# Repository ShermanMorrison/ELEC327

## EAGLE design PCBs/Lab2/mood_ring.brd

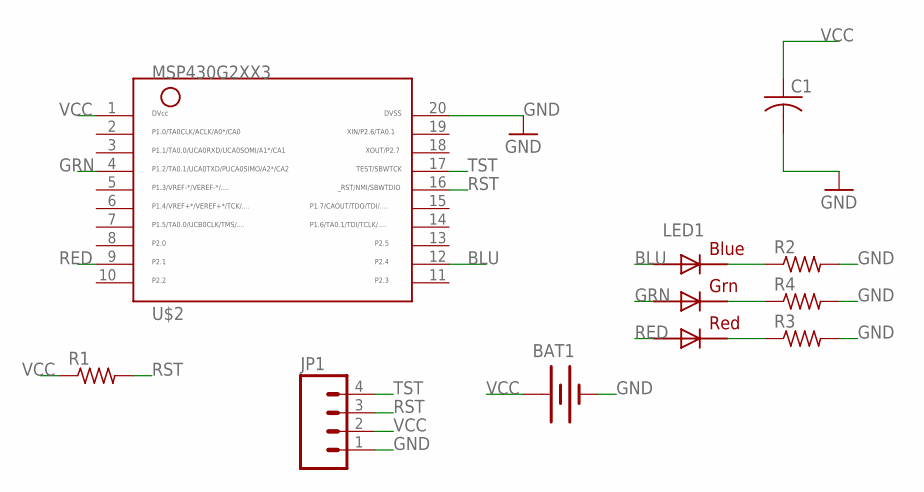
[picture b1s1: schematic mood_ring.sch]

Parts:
BAT1: BATTERYBU2032SM; BU2032SM
C1: C-USC1206; C1206
JP1: M04LOCK; 1X04_LOCK
LED1: RGBLED5050
R1, R2, R3, R4: R-US_R1206; R1206
U$2: MSP430G2XX3TSSOP; PW20

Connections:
BLU: LED1.3 (BLUE_A), U$2.12
GND: BAT1.P$2 (-), C1.2, JP1.1, R2.2, R3.2, R4.2, U$2.20
GRN: LED1.1 (GREEN_A), U$2.4
unnamed: LED1.4 (BLUE_C), R2.1
unnamed: LED1.5 (RED_C), R3.1
unnamed: LED1.6 (GREEN_C), R4.1
RED: LED1.2 (RED_A), U$2.9
RST: JP1.3, R1.2, U$2.16
TST: JP1.4, U$2.17
VCC: BAT1.P$1 (+), C1.1, JP1.2, R1.1, U$2.1

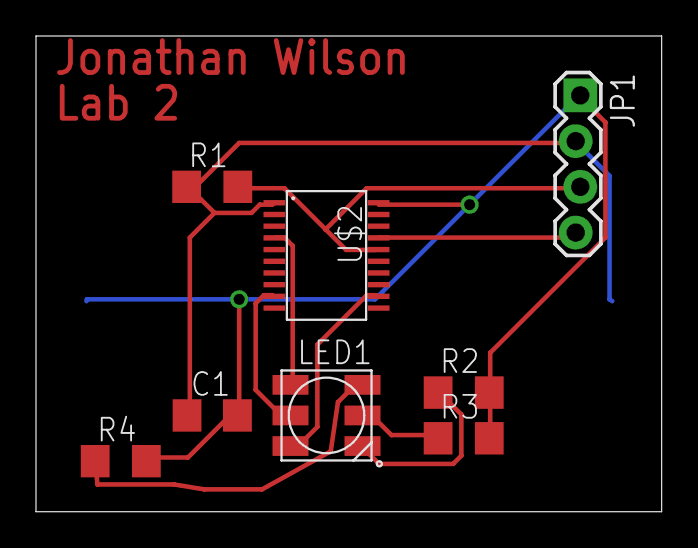
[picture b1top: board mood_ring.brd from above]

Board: 2 copper layers, 34.8 x 26.4 mm, 9 parts (1 on the bottom side), 10 nets.

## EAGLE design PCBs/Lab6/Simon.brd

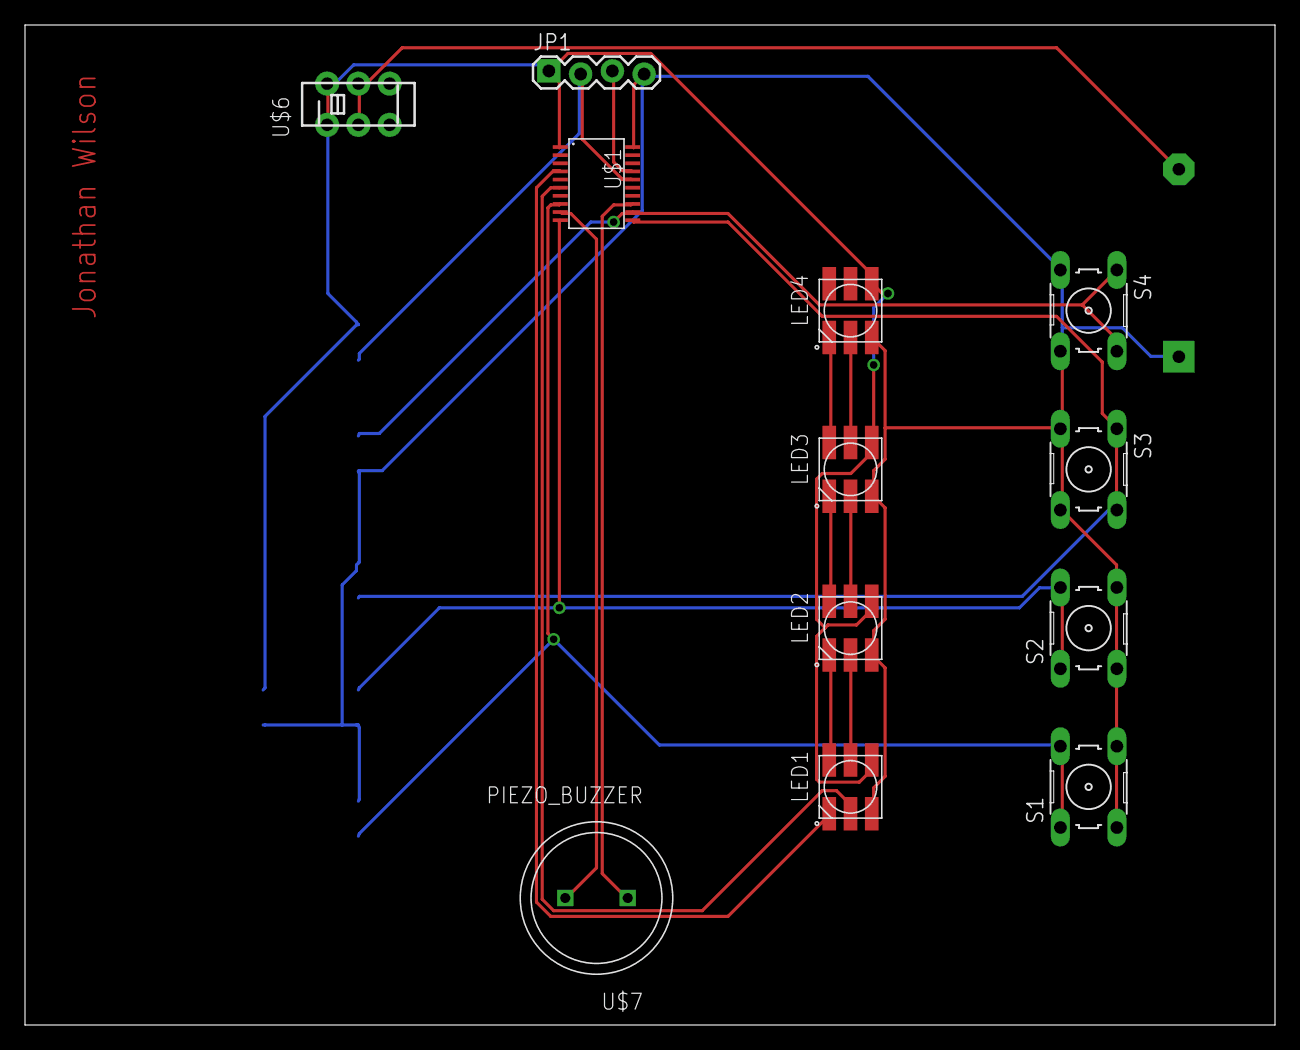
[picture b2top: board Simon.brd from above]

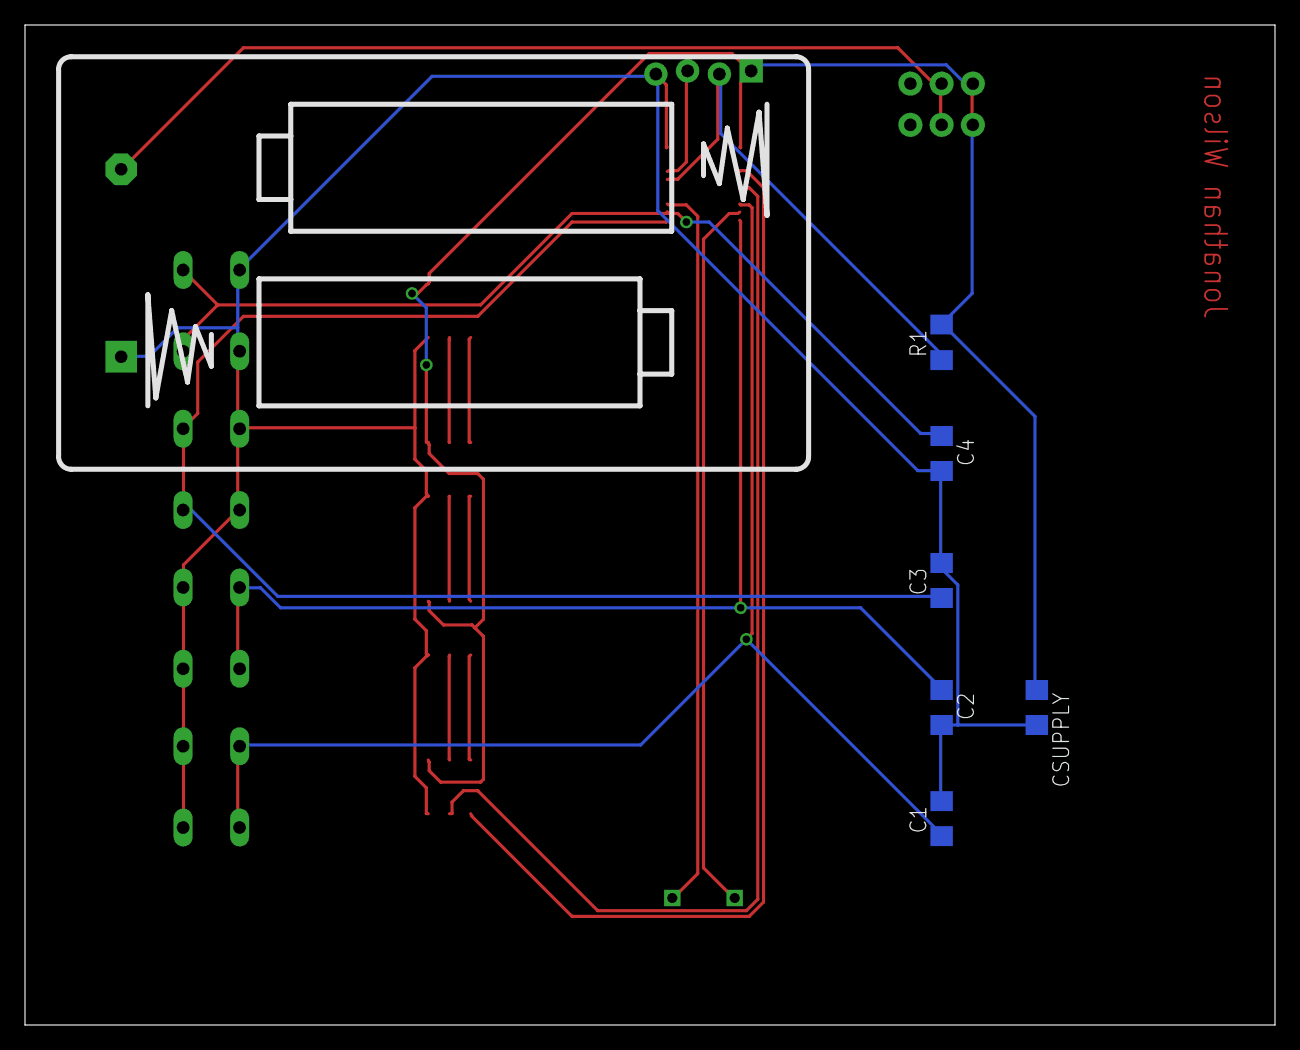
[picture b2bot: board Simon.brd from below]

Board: 2 copper layers, 100.0 x 80.0 mm, 19 parts (7 on the bottom side), 19 nets.

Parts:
BAT1: BATTERY_PACK_2AA
C1, C2, C3, C4: C1206
CSUPPLY: C1206
JP1: 1X04_LOCK
LED1, LED2, LED3, LED4: APA102; 5050
R1: R1206
S1, S2, S3, S4: B3F-10XX
U$1: MSP430G2XX3TSSOP; PW20
U$6: SWITCH_DPDT; JS_DPDT_TH
U$7: PIEZO_BUZZER

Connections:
BAT_VCC: BAT1.3V, U$6.2, U$6.5
GND: BAT1.GND, C1.2, C2.2, C3.2, C4.2, CSUPPLY.2, JP1.4, LED1.3, LED2.3, LED3.3, LED4.3, S1.3, S1.4, S2.3, S2.4, S3.3, S3.4, S4.3, S4.4, U$1.20
unnamed: LED1.6, LED2.1
unnamed: LED1.5, LED2.2
unnamed: LED2.6, LED3.1
unnamed: LED2.5, LED3.2
unnamed: LED3.6, LED4.1
unnamed: LED3.5, LED4.2
unnamed: LED1.1, U$1.4
unnamed: LED1.2, U$1.6
unnamed: U$1.9, U$7.P$2
unnamed: U$1.13, U$7.P$1
unnamed: C1.1, S1.1, S1.2, U$1.8
unnamed: C2.1, S2.1, S2.2, U$1.10
unnamed: C3.1, S3.1, S3.2, U$1.11
unnamed: C4.1, S4.1, S4.2, U$1.12
RST: JP1.2, R1.1, U$1.16
TEST: JP1.3, U$1.17
VCC: CSUPPLY.1, JP1.1, LED1.4, LED2.4, LED3.4, LED4.4, R1.2, U$1.1, U$6.1, U$6.4

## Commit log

2015-03-27 Made mood ring sch and brd
2015-03-27 Designed Lab 6 Simon brd

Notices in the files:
parts and their libraries:
SparkFun: Licensing: CC v3.0 Share-Alike You are welcome to use this library for commercial purposes.
